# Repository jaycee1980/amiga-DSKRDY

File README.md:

# amiga-DSKRDY
This is a small mod board that will provide a DSKRDY signal for drives which don't have one - commonly the case with "PC" disk drives.
Often there are modifications out there which claim to provide a !DSKRDY signal, but they are not actually proper !DSKRDY signals... this can cause issues with some disk routines and will show up as an issue in Amiga Test Kit, for example.

According to the Amiga spec, one should wait either 500ms OR for !DSKRDY to asset, after turning on the drive motor. Many trackloaders on the Amiga simply wait for !DSKRDY to be asserted, and will hang when it never happens. A good example of this is the Escom Amigas which shipped with a modified mainboard, which only diverted the !DSKCHG signal to the correct pin. The Amiga OS itself seems to always use a 500ms wait, so it is not affected by the lack of !DSKRDY.

As we don't have a real !DSKRDY signal to work from, the circuit works by simply asserting !DSKRDY roughly 500ms after !MTR and !SEL are asserted. It is designed onto a small 15x20mm PCB, which can be stuck to the bottom of a floppy drive and wires run to appropriate pads during modification.

## Whats in this repository

The schematic and board design are available, and were made with CadSoft EAGLE (burn in hell, Autodesk). 
There is also a PDF of the schematic.

The "gerber" folder contains suitable Gerber files for having the PCB manufactured. Any good PCB manufacturer should be able to do this - I personally use [JLCPCB](https://jlcpcb.com)

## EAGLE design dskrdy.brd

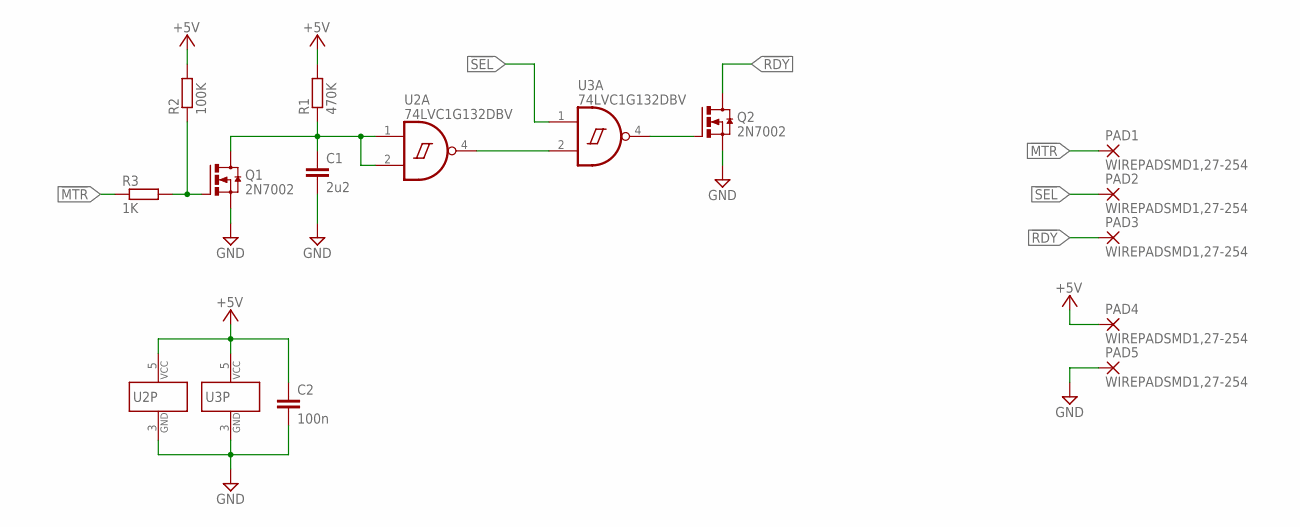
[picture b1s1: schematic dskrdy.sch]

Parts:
C1: 2u2; C0805
C2: 100n; C0805
PAD1, PAD2, PAD3, PAD4, PAD5: WIREPADSMD1,27-254; SMD1,27-2,54
Q1, Q2: 2N7002; SOT23
R1: 470K; R0805
R2: 100K; R0805
R3: 1K; R0805
U2, U3: 74LVC1G132DBV; SOT23-5

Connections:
!MTR: PAD1.1, R3.1
!RDY: PAD3.1, Q2.3 (D)
!SEL: PAD2.1, U3.1 (I0)
+5V: C2.1, PAD4.1, R1.2, R2.2, U2.5 (VCC), U3.5 (VCC)
GND: C1.2, C2.2, PAD5.1, Q1.2 (S), Q2.2 (S), U2.3 (GND), U3.3 (GND)
unnamed: Q1.1 (G), R2.1, R3.2
unnamed: C1.1, Q1.3 (D), R1.1, U2.1 (I0), U2.2 (I1)
unnamed: Q2.1 (G), U3.4 (O)
unnamed: U2.4 (O), U3.2 (I1)

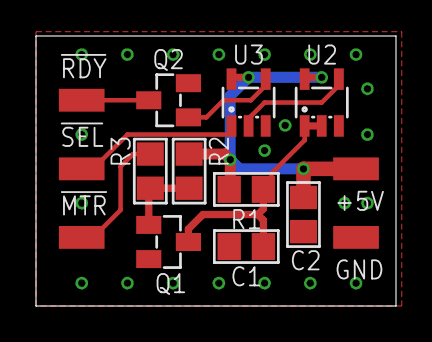
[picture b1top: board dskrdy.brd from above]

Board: 2 copper layers, 20.0 x 15.0 mm, 14 parts (0 on the bottom side), 9 nets.

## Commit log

2023-10-19 Added BOM
2023-10-19 More readable PDF schematic
